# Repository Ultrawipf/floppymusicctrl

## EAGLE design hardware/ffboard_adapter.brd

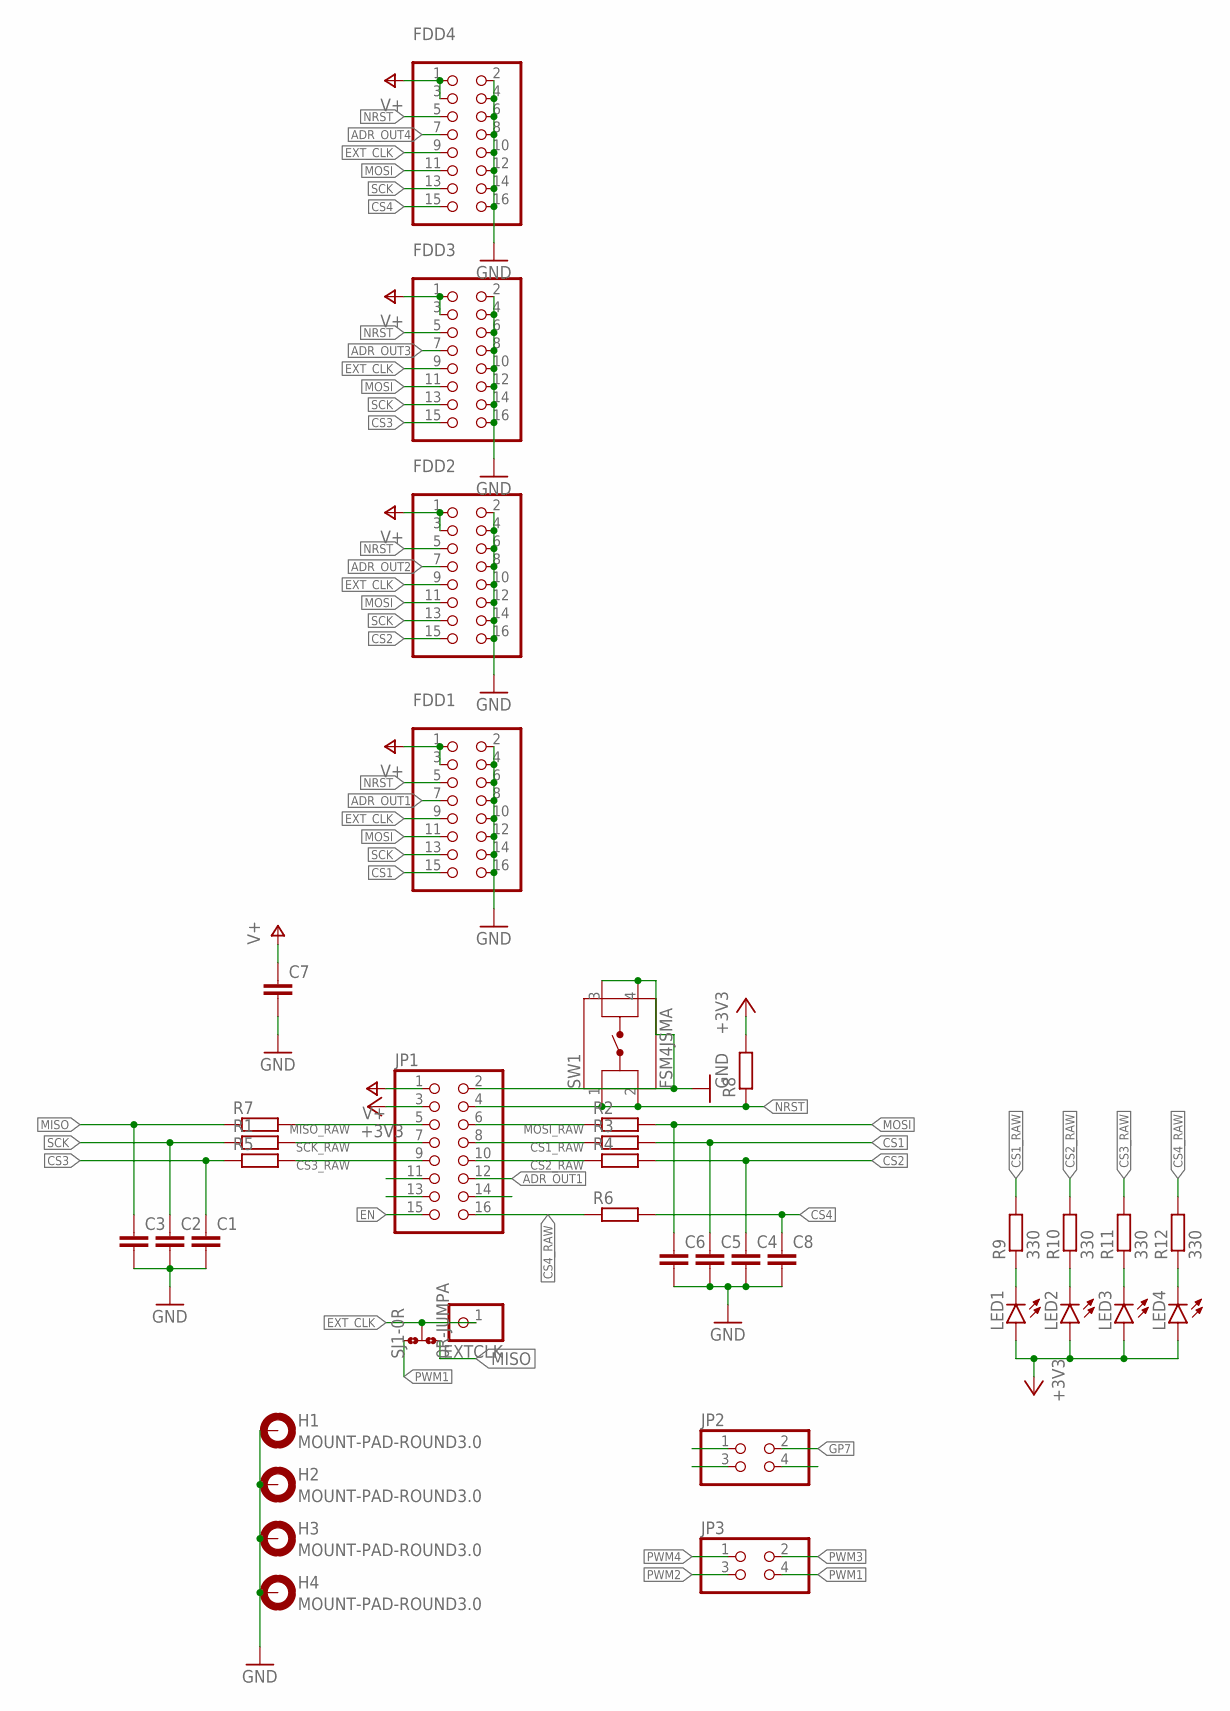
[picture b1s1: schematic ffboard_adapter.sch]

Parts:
C1, C2, C3, C4, C5, C6, C7, C8: C-EUC0603; C0603
EXTCLK: PINHD-1X1; 1X01
FDD1, FDD2, FDD3, FDD4: C221085; 2X08
H1, H2, H3, H4: MOUNT-PAD-ROUND3.0; 3,0-PAD
JP1: PINHD-2X8; 2X08
JP2, JP3: PINHD-2X2; 2X02
LED1, LED2, LED3, LED4: LEDSML0805; SML0805
R1, R2, R3, R4, R5, R6, R7, R8: R-EU_R0603; R0603
R9, R10, R11, R12: 330; R0603
SJ1: 0R-JUMPA; A0R-JMP
SW1: FSM4JSMA

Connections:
+3V3: JP1.3, LED1.A, LED2.A, LED3.A, LED4.A, R8.2
ADR_OUT1: FDD1.7, JP1.12
ADR_OUT2: FDD2.7
ADR_OUT3: FDD3.7
ADR_OUT4: FDD4.7
CS1: C5.1, FDD1.15, R3.2
CS1_RAW: JP1.8, R3.1, R9.2
CS2: C4.1, FDD2.15, R4.2
CS2_RAW: JP1.10, R4.1, R10.2
CS3: C1.1, FDD3.15, R5.1
CS3_RAW: JP1.9, R5.2, R11.2
CS4: C8.1, FDD4.15, R6.2
CS4_RAW: JP1.16, R6.1, R12.2
EN: JP1.15
EXT_CLK: EXTCLK.1, FDD1.9, FDD2.9, FDD3.9, FDD4.9, SJ1.2
GND: C1.2, C2.2, C3.2, C4.2, C5.2, C6.2, C7.2, C8.2, FDD1.2, FDD1.4, FDD1.6, FDD1.8, FDD1.10, FDD1.12, FDD1.14, FDD1.16, FDD2.2, FDD2.4, FDD2.6, FDD2.8, FDD2.10, FDD2.12, FDD2.14, FDD2.16, FDD3.2, FDD3.4, FDD3.6, FDD3.8, FDD3.10, FDD3.12, FDD3.14, FDD3.16, FDD4.2, FDD4.4, FDD4.6, FDD4.8, FDD4.10, FDD4.12, FDD4.14, FDD4.16, H1.B3,0, H2.B3,0, H3.B3,0, H4.B3,0, JP1.2, SW1.3, SW1.4
GP7: JP2.2
MISO: C3.1, R7.1, SJ1.3
MISO_RAW: JP1.5, R7.2
MOSI: C6.1, FDD1.11, FDD2.11, FDD3.11, FDD4.11, R2.2
MOSI_RAW: JP1.6, R2.1
unnamed: LED1.C, R9.1
unnamed: LED2.C, R10.1
unnamed: LED3.C, R11.1
unnamed: LED4.C, R12.1
NRST: FDD1.5, FDD2.5, FDD3.5, FDD4.5, JP1.4, R8.1, SW1.1, SW1.2
PWM1: JP3.4, SJ1.1
PWM2: JP3.3
PWM3: JP3.2
PWM4: JP3.1
SCK: C2.1, FDD1.13, FDD2.13, FDD3.13, FDD4.13, R1.1
SCK_RAW: JP1.7, R1.2
V+: C7.1, FDD1.1, FDD1.3, FDD2.1, FDD2.3, FDD3.1, FDD3.3, FDD4.1, FDD4.3, JP1.1

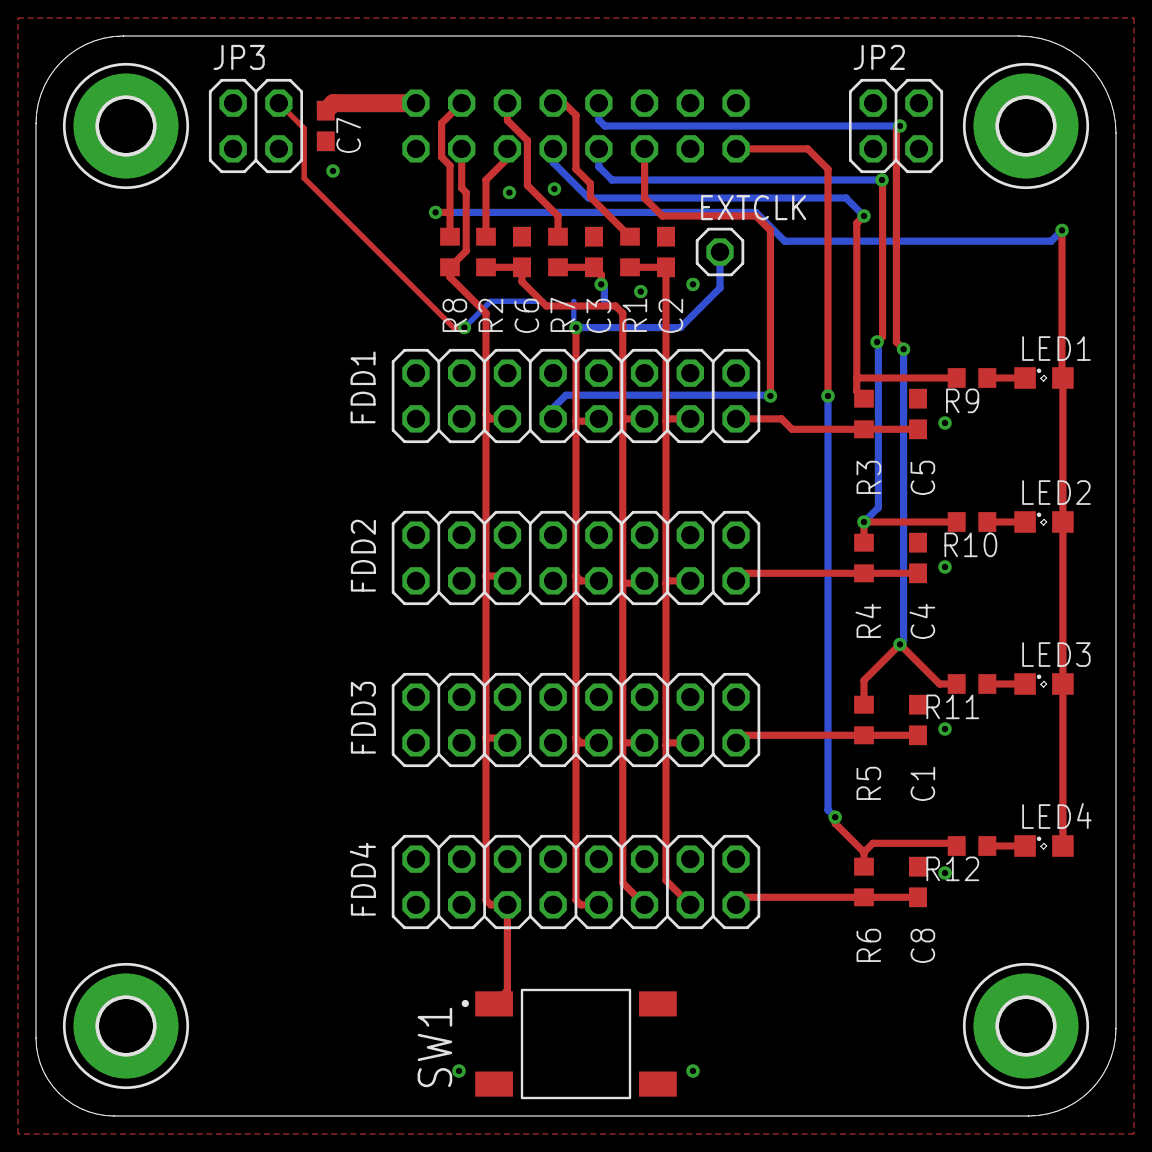
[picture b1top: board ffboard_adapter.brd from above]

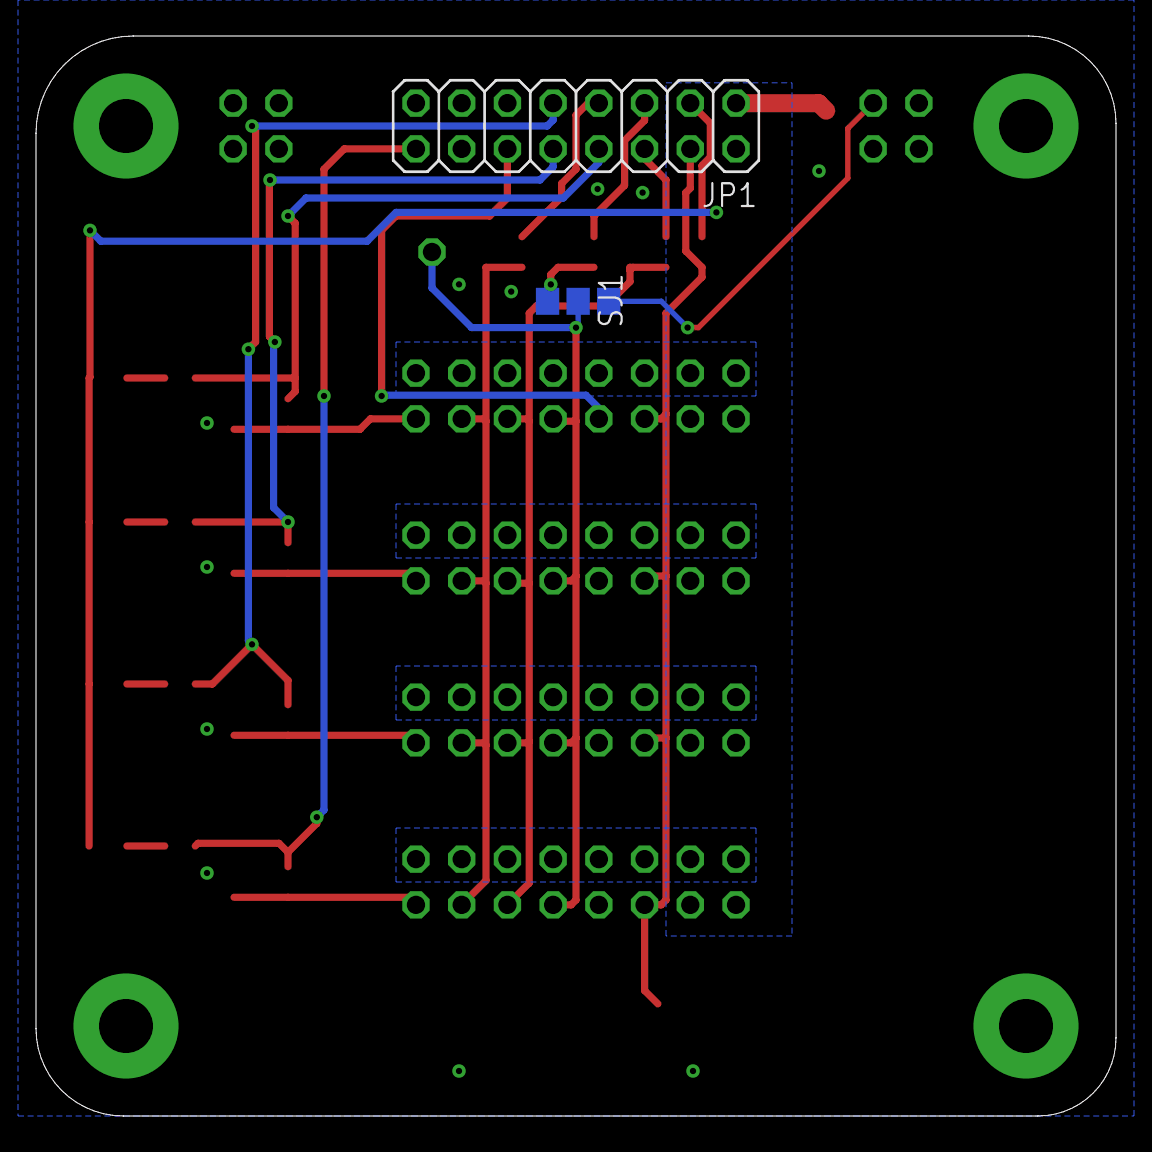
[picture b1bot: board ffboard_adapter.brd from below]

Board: 2 copper layers, 60.0 x 60.0 mm, 38 parts (2 on the bottom side), 25 nets.

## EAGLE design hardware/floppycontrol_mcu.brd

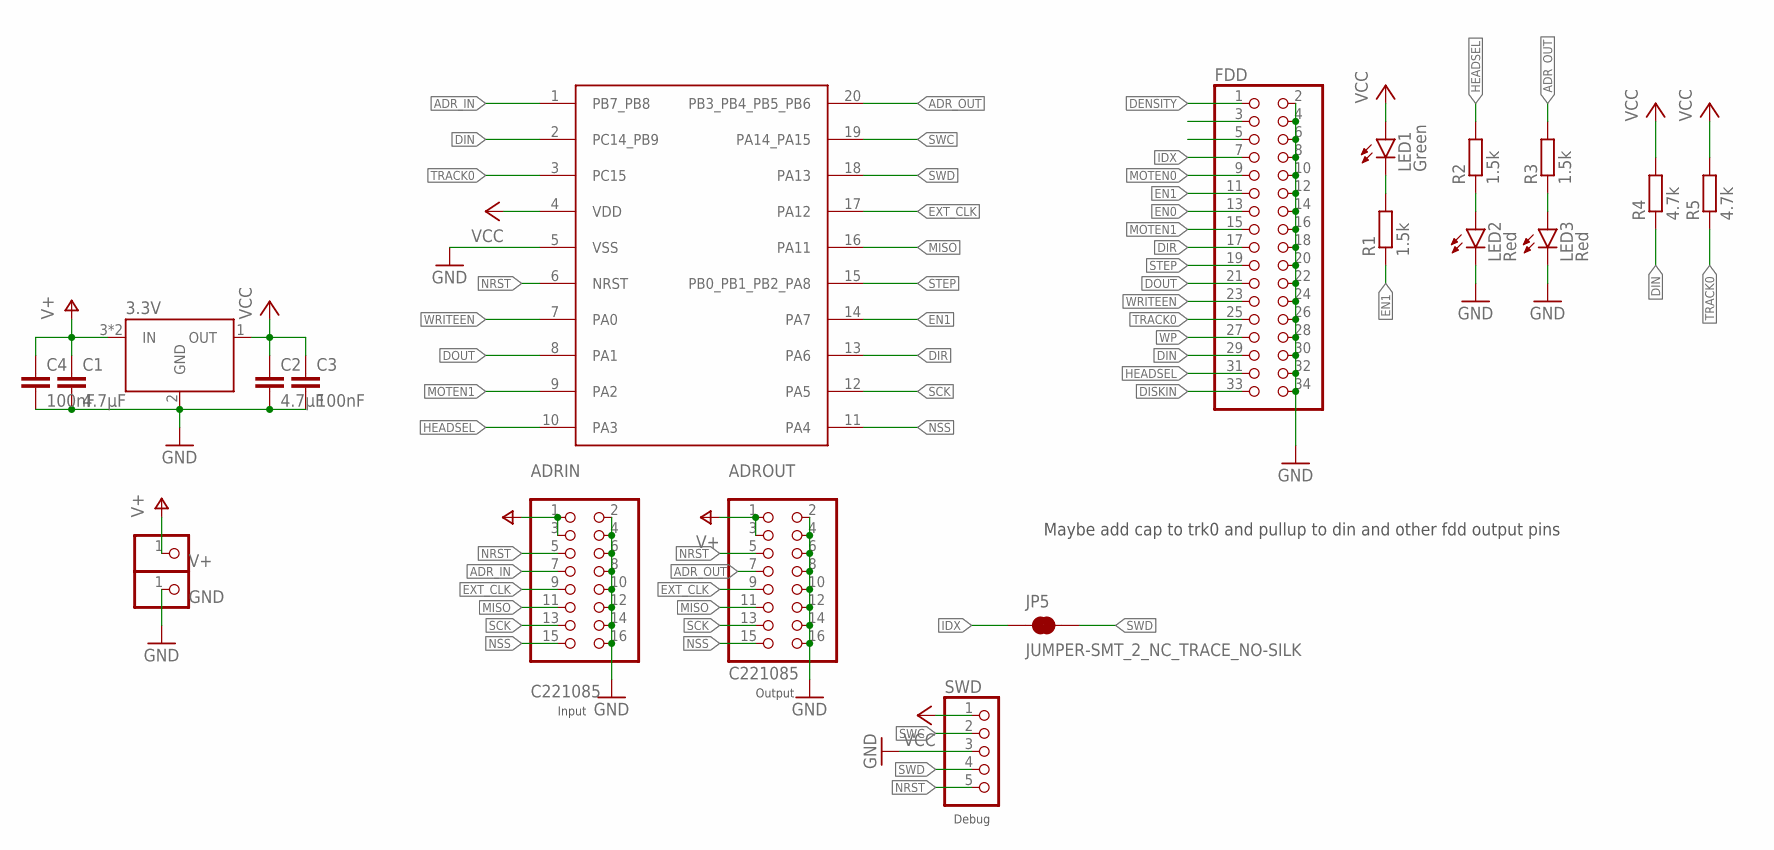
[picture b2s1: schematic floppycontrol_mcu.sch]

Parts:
ADRIN: C221085; 2X08/90
ADROUT: C221085; 2X08/90
C1, C2: 4.7µF; C0603
C3, C4: 100nF; C0603
FDD: PINHD-2X17/90; 2X17/90
GND: PINHD-1X1; 1X01
JP5: JUMPER-SMT_2_NC_TRACE_NO-SILK; SMT-JUMPER_2_NC_TRACE_NO-SILK
LED1: Green; CHIP-LED0805
LED2, LED3: Red; CHIP-LED0805
R1, R2, R3: 1.5k; R0603
R4, R5: 4.7k; R0603
SWD: PINHD-1X5; 1X05
U1: STM32G030F6P6TSSOP20; TSSOP20
U2: 3.3V; SOT89-R
V+: PINHD-1X1; 1X01

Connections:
ADR_IN: ADRIN.7, U1.1 (PB7_PB8)
ADR_OUT: ADROUT.7, R3.2, U1.20 (PB3_PB4_PB5_PB6)
DENSITY: FDD.1
DIN: FDD.29, R4.1, U1.2 (PC14_PB9)
DIR: FDD.17, U1.13 (PA6)
DISKIN: FDD.33
DOUT: FDD.21, U1.8 (PA1)
EN0: FDD.13
EN1: FDD.11, R1.1, U1.14 (PA7)
EXT_CLK: ADRIN.9, ADROUT.9, U1.17 (PA12)
GND: ADRIN.2, ADRIN.4, ADRIN.6, ADRIN.8, ADRIN.10, ADRIN.12, ADRIN.14, ADRIN.16, ADROUT.2, ADROUT.4, ADROUT.6, ADROUT.8, ADROUT.10, ADROUT.12, ADROUT.14, ADROUT.16, C1.2, C2.2, C3.2, C4.2, FDD.2, FDD.4, FDD.6, FDD.8, FDD.10, FDD.12, FDD.14, FDD.16, FDD.18, FDD.20, FDD.22, FDD.24, FDD.26, FDD.28, FDD.30, FDD.32, FDD.34, GND.1, LED2.C, LED3.C, SWD.3, U1.5 (VSS), U2.2 (GND)
HEADSEL: FDD.31, R2.2, U1.10 (PA3)
IDX: FDD.7, JP5.1
MISO: ADRIN.11, ADROUT.11, U1.16 (PA11)
MOTEN0: FDD.9
MOTEN1: FDD.15, U1.9 (PA2)
unnamed: LED1.C, R1.2
unnamed: LED2.A, R2.1
unnamed: LED3.A, R3.1
NRST: ADRIN.5, ADROUT.5, SWD.5, U1.6 (NRST)
NSS: ADRIN.15, ADROUT.15, U1.11 (PA4)
SCK: ADRIN.13, ADROUT.13, U1.12 (PA5)
STEP: FDD.19, U1.15 (PB0_PB1_PB2_PA8)
SWC: SWD.2, U1.19 (PA14_PA15)
SWD: JP5.2, SWD.4, U1.18 (PA13)
TRACK0: FDD.25, R5.1, U1.3 (PC15)
V+: ADRIN.1, ADRIN.3, ADROUT.1, ADROUT.3, C1.1, C4.1, U2.3 (IN), U2.4 (IN), V+.1
VCC: C2.1, C3.1, LED1.A, R4.2, R5.2, SWD.1, U1.4 (VDD), U2.1 (OUT)
WP: FDD.27
WRITEEN: FDD.23, U1.7 (PA0)

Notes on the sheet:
Input
Output
Debug
Maybe add cap to trk0 and pullup to din and other fdd output pins

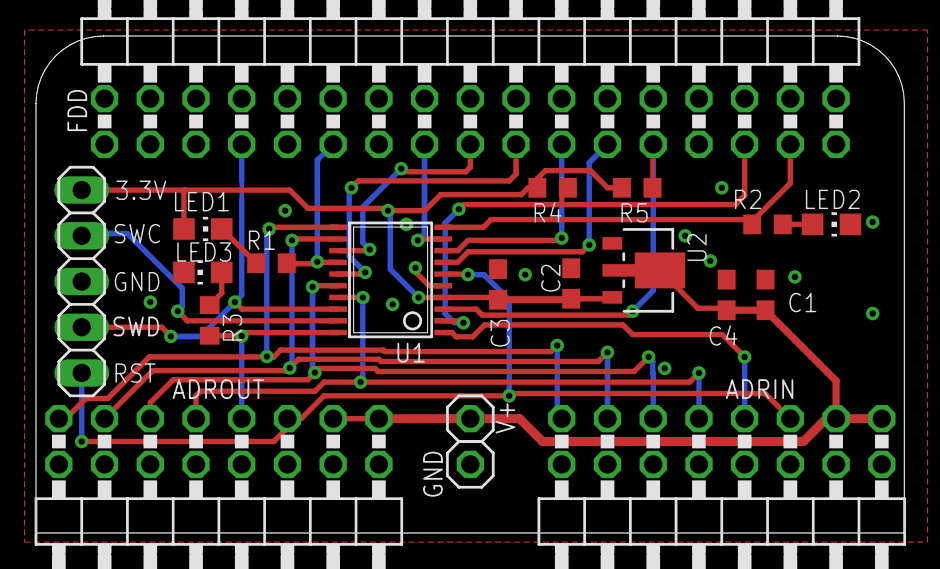
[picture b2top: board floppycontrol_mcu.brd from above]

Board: 2 copper layers, 48.2 x 27.6 mm, 21 parts (1 on the bottom side), 25 nets.

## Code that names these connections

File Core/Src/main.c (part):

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  MX_TIM14_Init();
  MX_TIM17_Init();
  /* USER CODE BEGIN 2 */
  // Set DIN pin to pullup
//  GPIO_InitTypeDef GPIO_InitStruct = {0};
//  GPIO_InitStruct.Pin = FDD_DIN_Pin;
//  GPIO_InitStruct.Mode = GPIO_MODE_AF_PP;
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//  GPIO_InitStruct.Speed = GPIO_SPEED_FREQ_HIGH;
//  HAL_GPIO_Init(FDD_DIN_GPIO_Port, &GPIO_InitStruct);

  // TODO use PA12 as ETR for tim1
  initializeTimers();
  findAddress();
  initializeComms();
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                          |ENABLE_Pin, GPIO_PIN_SET);

  /*Configure GPIO pin Output Level */
  HAL_GPIO_WritePin(ADR_OUT_GPIO_Port, ADR_OUT_Pin, GPIO_PIN_RESET);

  /*Configure GPIO pin : ADR_IN_Pin */
  GPIO_InitStruct.Pin = ADR_IN_Pin;
  GPIO_InitStruct.Mode = GPIO_MODE_IT_RISING_FALLING;
  GPIO_InitStruct.Pull = GPIO_PULLUP;
  HAL_GPIO_Init(ADR_IN_GPIO_Port, &GPIO_InitStruct);

  /*Configure GPIO pin : FDD_TRK0_Pin */
  GPIO_InitStruct.Pin = FDD_TRK0_Pin;
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  GPIO_InitStruct.Speed = GPIO_SPEED_FREQ_HIGH;
  HAL_GPIO_Init(ENABLE_GPIO_Port, &GPIO_InitStruct);

  /*Configure GPIO pin : ADR_OUT_Pin */
  GPIO_InitStruct.Pin = ADR_OUT_Pin;
  GPIO_InitStruct.Mode = GPIO_MODE_OUTPUT_PP;
  GPIO_InitStruct.Pull = GPIO_NOPULL;
  GPIO_InitStruct.Speed = GPIO_SPEED_FREQ_MEDIUM;
  HAL_GPIO_Init(ADR_OUT_GPIO_Port, &GPIO_InitStruct);

  /* EXTI interrupt init*/
  HAL_NVIC_SetPriority(EXTI4_15_IRQn, 2, 0);
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
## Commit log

2023-07-14 Usable midi
2023-07-14 Added hardware files

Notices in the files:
Core/Src/main.c:
Copyright (c) 2022 STMicroelectronics.
All rights reserved.
This software is licensed under terms that can be found in the LICENSE file
parts and their libraries:
SparkFun-Jumpers: Licensing: Creative Commons ShareAlike 4.0 International - https://creativecommons.org/licenses/by-sa/4.0
